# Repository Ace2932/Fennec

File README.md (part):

# Fennec — Autonomous Quadruped

> **Fennec** is an autonomous quadruped I'm building on the [NovaSM3](https://github.com/cguweb-com/Arduino-Projects/tree/main/Nova-SM3) platform (by Chris Locke / [novaspotmicro.com](https://novaspotmicro.com/)) — rebuilt around a unified Feetech STS3215 TTL servo bus, NVIDIA Jetson Orin Nano Super compute, and ROS 2 Humble, as a platform for Vision-Language-Action (VLA) model deployment, 3D SLAM, and autonomous mobile manipulation.

**Status:** 🔧 Phase 1 — hardware bring-up + sim training. **Both PCBs ordered 2026-07-01 (JLCPCB)** — power board v2 (Pattern B bus master, INA226 rail telemetry, Phase-4 arm rail provisioned) + logic board. Firmware critical-path green (safety FSM, watchdogs, servo limits, joint-map loader; rostest suites in CI). Legs (**leg_v6**) printing; chassis-integration + CAD fit-gate audits closed; measured leg geometry → URDF + IK green. **🎉 RL locomotion walks in sim** (MuJoCo MJX + Brax PPO, 2026-07-16) — stair-climb curriculum in progress. **See [`STATUS.md`](./STATUS.md) for the live blockers / next-actions board.**
**Platform:** Quadruped (12 DOF) — arm (6-DOF, Phase 4 future) on shelf
**Compute:** NVIDIA Jetson Orin Nano Super 8GB
**Middleware:** ROS 2 Humble
**Last updated:** July 22, 2026

---

> **Design outline:** [`docs/design-outline.md`](./docs/design-outline.md) — the canonical top-level design document (architecture, doctrines, lane status). Start there.

## Table of Contents

1. [Project Overview](#project-overview)
2. [Differences from Stock NovaSM3](#differences-from-stock-novasm3)
3. [Hardware Architecture](#hardware-architecture)
4. [Software Architecture](#software-architecture)
5. [Power System](#power-system)
6. [Network Topology](#network-topology)
7. [Bill of Materials](#bill-of-materials)
8. [Build Roadmap](#build-roadmap)
9. [Pre-Assembly Test Sequence](#pre-assembly-test-sequence)
10. [Setup Guide](#setup-guide)
11. [Open Decisions](#open-decisions)
12. [References & Credits](#references--credits)

---

## Project Overview

This project is a heavily modified fork of the open-source NovaSM3 quadruped, redesigned to serve as a research platform for embodied AI. Stock Nova uses PWM hobby servos and a Raspberry Pi running custom locomotion code. This build replaces:

- **12 servos** with Feetech STS3215 TTL bus servos for unified protocol, real-time joint feedback (position, load, temperature, voltage), and elimination of PWM wiring complexity. Six additional STS3215 (arm) remain on shelf for Phase 4.
- **The Pi** with an NVIDIA Jetson Orin Nano Super (67 TOPS sparse INT8 / ~33 TOPS dense; 8GB RAM tight but workable for VLA inference + ROS 2 + SLAM — see Phase 4 notes). Real-time servo bus is offloaded to a Teensy 4.1 (Pattern B); Jetson runs ROS 2 + perception only.
- **The stock perception** with Intel RealSense D456 (depth + RGB + IMU) and Unitree L2 4D LiDAR (360° × 96° FOV, 30m range)
- **The stock locomotion stack** with ROS 2 Humble (Jetson) + Teensy bus master (Pattern B) + Nav2 + RTAB-Map / POINT-LIO

The arm is carried over from a prior SO-ARM101 build, also Feetech-based. **v1 build scope: quadruped only (12 servos active).** Arm install + integration is Phase 4 future work — bus IDs 13-18 and the 7.5V arm-rail buck footprint (D42V55F7) are reserved on the PCB v6 redesign so the future install is a populate-and-go.

### Goals

- ✅ Unified TTL servo bus across locomotion (12 servos v1; future-ready for 18 with arm)
- 🔧 ROS 2 locomotion via micro-ROS bridge to Teensy 4.1 (Teensy owns the Feetech bus in Pattern B; FE-URT-1 retained as bench fallback)
- 🔧 RL locomotion policy trained in simulation (`sim/nova_mjx`, MuJoCo MJX + Brax PPO) — ✅ walks in sim (2026-07-16); terrain curriculum + stair climbing + sim2real transfer in progress
- 📋 3D SLAM using LiDAR + visual-inertial fusion (POINT-LIO baseline, RTAB-Map comparison)
- 📋 Autonomous navigation (Nav2) on legged platform with stair climbing
- 📋 VLA fine-tuning and deployment for mobile manipulation tasks
- 📋 Open-source documentation of every design decision for community reuse

---

## Differences from Stock NovaSM3

| Subsystem | Stock NovaSM3 | This Build |
|-----------|---------------|------------|
| Compute (main) | Raspberry Pi 4 | NVIDIA Jetson Orin Nano Super 8GB |
| Compute (MCU) | Teensy 4.0 | Teensy 4.1 (more RAM + SD slot) |
| Aux MCU | Arduino Nano | Arduino Nano (kept, peripherals only) |
| Locomotion servos | 12× PWM hobby servos | 12× Feetech STS3215 (4× 12V/30kg hip, 8× 7.4V/19kg femur/tibia) |
| Arm | None (stock) | 6× Feetech STS3215 from SO-ARM101 — **on shelf, Phase 4** |
| Servo protocol | PWM (one signal per servo) | TTL half-duplex serial bus (daisy-chained) |
| Perception | None / optional | RealSense D456 + Unitree L2 LiDAR |
| Middleware | Custom Arduino loops | ROS 2 Humble + micro-ROS |
| Power | 3S 11.1V LiPo | 4S 14.8V LiPo + Pololu buck rails (7.5V leg / 12V hip / 12V L2 dedicated / 12V Jetson / 5V aux). XL4016 dropped after capacity audit. |
| Print materials | PLA / PETG | PA6-CF (structural) / PETG-CF (secondary) / TPU 95A (foot pads + strain relief) |
| Print feed | Direct from spool | **Creality SpacePi X4 dryer → 4 mm PTFE Bowden → P1S** (AMS HF bypassed for PA6-CF — re-absorbs moisture in AMS chamber, defeats pre-drying) |

### Why redesign the PCB (v5.2b → v6)

After the v3.2 architecture audit, the stock Nova PCB v5.2b can't host the upgraded power tree (Pololu modules, INA226 telemetry, hard-cutoff MOSFET, E-stop chain) or the Pattern A/B bus master selector. The redesign retains the spirit of the stock board (Arduino Nano aux slot, battery input geometry) and adds the new safety + power architecture. Full feature set in [`hardware/pcb-mods/README.md`](./hardware/pcb-mods/README.md).

### What carries over from Nova v5.2b

- Arduino Nano slot for aux peripherals — **v3.5 cut**: OLED + WS2812B only (PIR / ultrasonic / MP3 / MPU-6050 removed; D456 + L2 perception stack covers their roles)
- Battery input + reverse polarity protection geometry (replicated with MOSFET-based reverse protection instead of diode)
- Power switch, voltmeter, fuse (MRBF-30 in Blue Sea 5191 block, OFF-board at pack — ~9 kA AIC @ 16.8 V clears this pack's ~1.5–3 kA dead-short with 3–4× margin; ANL's 6 kA rejected, Class T superseded 2026-06-12)

### What changes

- All 12 PWM servo output headers removed (Feetech bus is daisy-chain TTL, doesn't use PWM)
- XL4016 buck footprints → Pololu D42V110-class module footprints
- Add: SN74LVC125A half-duplex driver (Pattern B prep), INA226 ×3, E-stop chain, hard-cutoff MOSFET, **MRBF-30 fuse OFF-board** (Blue Sea 5191 at pack — F1 not on PCB), bulk caps at injection points, bus-integrity footprints (series R + ferrite beads), reserved arm-rail buck footprint

---

## Hardware Architecture

### Block diagram

```
┌────────────────────────────────────────────────────────────────────┐
│                  NVIDIA Jetson Orin Nano Super 8GB                 │
│                          (ROS 2 Humble)                            │
│   • Nav2, SLAM, VLA inference, sensor fusion                       │
│   • Sends /joint_commands to Teensy via micro-ROS over USB         │
│   • Built-in WiFi 5 (802.11ac/ab/gn) per NVIDIA P3766 spec sheet   │
└──┬──────────┬─────────────┬─────────────┬───────────────────────────┘
   │ USB-C    │ USB 3.1     │ Ethernet    │ USB (micro-ROS transport)
   │          │             │             │
┌──▼───────┐ ┌▼───────────┐ ┌▼───────────┐ ┌▼─────────────────────────┐
│ Realsense│ │ FE-URT-1   │ │ Gig switch │ │ Teensy 4.1 (BUS MASTER v1)│
│ D456     │ │ (debug/    │ │            │ │  • Real-time gait loop    │
│ (depth + │ │  bench     │ │ ◄─ L2 ─►   │ │  • UART → SN74LVC125A → bus   │
│  RGB +   │ │  fallback) │ │            │ │  • INA226 I²C reader      │
│  IMU)    │ │            │ └────────────┘ │  • E-stop GPIO sense      │
└──────────┘ └────┬───────┘                │  • micro-ROS over USB     │
                  ↓                        └──┬────────────────────────┘
              (JP_BUS_MASTER                  │ UART → SN74LVC125A half-duplex
               solder bridge:                 │ (active v1 path)
               default = B,                   │
               flip to A for ID setup)        ▼
                                  ┌───────────────────────┐
                                  │ 12× STS3215 (TTL bus) │
                                  │ per-leg: FL1-3 FR4-6  │
                                  │ RL7-9 RR10-12 (h/f/t) │
                                  │  IDs 13-18: ⏸ arm    │
                                  │  (Phase 4 reserved)   │
                                  └───────────────────────┘

       ┌──── Arduino Nano (USB-serial bridge from Jetson:
       │                   OLED + WS2812B status LEDs) ────┐
       │                                                                  │
       └──────────────────────────────────────────────────────────────────┘
```

### Servo configuration

| Joint group | Count | Servo | Voltage | Bus IDs | Status |
|-------------|-------|-------|---------|---------|--------|
| Hips | 4 | STS3215 30kg | 12V | 1-4 | v1 active |
| Femur + tibia | 8 | STS3215 19kg | 7.4V | 5-12 | v1 active |
| Arm (shoulder + elbow) | 3 | STS3215 19kg | 7.4V | 13-15 | ⏸ Phase 4 — reserved |
| Arm (wrist + gripper) | 3 | STS3215 19kg | 7.4V | 16-18 | ⏸ Phase 4 — reserved |

**v1 build = 12 active servos** on a single daisy-chained TTL bus, 2 active servo-power voltage levels (7.5V leg, 12V hip) plus dedicated 12V/2.6A L2 LiDAR buck and 12V/3A Jetson buck. Bus master is the **Teensy 4.1 (Pattern B)** via a SN74LVC125A half-duplex driver. Bus IDs 13-18 and the 7.4V arm rail (D42V55F7 footprint) reserved on PCB v6 for Phase 4 arm install — populate-and-go.

### Bus master pattern

**Pattern B is v1 default.** Both paths live on PCB v6 via solder bridge `JP_BUS_MASTER`.

- **Pattern B (v1 active):** Teensy 4.1 hardware UART → SN74LVC125A quad tri-state buffer (half-duplex driver) → TTL bus pads. Bare-metal real-time loop at 200-500 Hz. Jetson sends joint targets via micro-ROS over USB; Teensy translates to bus reads/writes. Survives Jetson restarts, kernel preemption, CUDA stalls, journald flushes — none of which affect bus servicing. Solder bridge defaults to B.
- **Pattern A (bench / debug fallback):** Jetson → USB → FE-URT-1 → TTL bus. Use for: initial servo ID assignment with the Feetech FD / SCServo SDK Python tools from a workstation (simpler than booting micro-ROS for ID setup), debug if Teensy firmware misbehaves, post-mortem inspection of bus traffic. Flip `JP_BUS_MASTER` to A.

**Why B as default (decision history):** Linux is not a real-time OS. USB-CDC latency on Jetson runs 1-10 ms typical, 50 ms+ under load. **What Pattern B actually buys:** bus-servicing isolation on the Teensy side — UART transactions to all 12 servos complete on time even when Jetson is jittery, so the bus doesn't time out and servos don't fault. The gait controller still runs on Jetson and publishes targets at 100 Hz, so Jetson's command rate is still Linux-bounded; the Teensy oversamples at 200-500 Hz against the last received target, holding it through Jetson stalls. A 100 ms Linux freeze becomes "robot pauses mid-step," not "bus dies and robot falls." v3.2 originally defaulted to A with "migrate if measurement forces it" — v3.3 flips to B-default because the migration cost is just populating one $1 IC + Phase 1 firmware work, and skipping the measure-then-migrate path eliminates a Phase 2 surprise. See Open Decisions row 5.

**Phase 1 acceptance gate (revised):** Pattern B's real guarantee is bus-servicing isolation on the Teensy side, not full RTT through Linux. Two mandatory criteria + one sanity check:
1. **Teensy local loop tick jitter p99 <100 µs** over 60 seconds (bare-metal — easy if firmware is right)
2. **`/joint_commands` arrival rate ≥99% of 100 Hz target** over 60 seconds (Jetson + uROS healthy)
3. *(Sanity)* End-to-end RTT median <5 ms, p99 <20 ms — Linux-bounded, not a hard pass/fail

If (1) misses → debug Teensy firmware (DMA vs ISR, UART config). If (2) misses → debug Jetson uROS / USB cable / CPU contention. If only (3) is high → accept: Teensy holds last command under Jetson jitter, robot stays stable.

---

## Software Architecture

### ROS 2 stack (target)

```
┌──────────────────────────────────────────────┐
│             Application Layer                │
│  • Behavior tree / mission FSM               │
│  • VLA policy node                           │
│  • Teleop bridge                             │
└──────────────────────────────────────────────┘
┌──────────────────────────────────────────────┐
│            Navigation Layer                  │
│  • Nav2 (planning + control)                 │
│  • robot_localization (EKF)                  │
└──────────────────────────────────────────────┘
┌──────────────────────────────────────────────┐
│              Perception Layer                │
│  • RTAB-Map / POINT-LIO (3D SLAM)            │
│  • realsense2_camera                         │
│  • unitree_lidar_ros2                        │
└──────────────────────────────────────────────┘
┌──────────────────────────────────────────────┐
│            Locomotion Layer (Jetson)         │
│  • Gait controller (8-phase walk)            │
│  • 3-DOF-per-leg IK solver                   │
│  • Publishes /joint_commands                 │
│  • Subscribes /joint_states                  │
└──────────────────────────────────────────────┘
┌──────────────────────────────────────────────┐
│        Bus Master Layer (Teensy 4.1)         │
│  • micro-ROS client (USB transport)          │
│  • SCServo SDK port — Feetech bus driver     │
│  • SN74LVC125A half-duplex TX/RX gating          │
│  • Real-time loop @ 200-500 Hz               │
│  • INA226 I²C reader → /diagnostics          │
└──────────────────────────────────────────────┘
┌──────────────────────────────────────────────┐
│              Hardware Layer                  │
│  • Feetech STS3215 bus (12 servos v1)        │
│  • IMU driver, aux peripheral I/O            │
└──────────────────────────────────────────────┘
```

### Key software components

| Component | Purpose | Status |
|-----------|---------|--------|
| ROS 2 Humble | Middleware | 📋 Install on Jetson |
| `librealsense2` | RealSense SDK | 📋 ARM64 build |
| `realsense2_camera` | ROS 2 wrapper for D456 | 📋 apt install |
| `unilidar_sdk2` | Unitree L2 SDK | ✅ Built green on Jetson (official `unitreerobotics/unilidar_sdk2`, **not discodyer fork** — official now bundles ROS 2 wrapper) |
| `unitree_lidar_ros2` | ROS 2 wrapper for L2 | ✅ Built + streaming. Use **Ace2932/unilidar_sdk2 `fix/imu-bridge-double-call` branch** — fixes upstream IMU bridge bug where `getImuData()` is called twice in `timer_callback()`, draining the SDK queue before publish. |
| POINT-LIO | LiDAR-inertial SLAM | 📋 Eval first |
| RTAB-Map | Visual-LiDAR SLAM | 📋 Compare with POINT-LIO |
| Nav2 | Autonomous navigation | 📋 Phase 3 |
| robot_localization | EKF sensor fusion | 📋 Phase 2 |
| micro-ROS (Teensy) | Embedded ROS 2 | 📋 Phase 2 |
| SCServo SDK (Teensy port) | Feetech bus driver running on Teensy in Pattern B | ⚠️ Already familiar from SO-ARM101 — port to TeensyDuino in Phase 1 |
| MJX/Brax sim (`sim/nova_mjx`) | RL locomotion training — MuJoCo MJX physics, Brax PPO, procedural terrain curriculum (rough / steps / stairs), domain randomization | 🔧 Walks in sim (flat trot, 2026-07-16); stair-climb curriculum active |

---

## Power System

### Voltage rails

```
4S LiPo 14.8V nominal (12.8-16.8V)
   │  MRBF-30 fuse (off-board) · MOSFET reverse-protection · MOSFET hard-cutoff @12.4V · E-stop NC (servo rails only)
   │
   ├── Pololu D42V110F7  ──► 7.5V/10A ──► 8× STS3215 19kg femur/tibia
   │       (star injection at 4 points along chain, bulk caps near point of load)
   │
   ├── Pololu D42V110F12 ──► 12V/9A   ──► 4× STS3215 30kg hips ONLY
   │
   ├── Pololu D24V22F12  ──► 12V/2.6A ──► Unitree L2 LiDAR (1A, LC filter on output)
   │
   ├── Pololu D42V55F12  ──► 12V/~3A  ──► Jetson Orin Nano (barrel jack)
   │
   ├── [reserved D42V55F7] ► 7.5V/3-8A ──► 6× STS3215 arm (Phase 4 — footprint unstuffed)
   │
   └── UBEC 5V/5A ──► 5V rail ──► fans, aux 5V peripherals

   INA226 ×3 (leg 7.5V, hip 12V, Jetson 12V) ──► I²C ──► Teensy 4.1 ──► ROS 2 diagnostics
   13.0V comparator ──► Teensy GPIO ──► /battery_low ──► Jetson clean shutdown
   12.4V comparator ──► MOSFET ──► breaks battery feed (autonomous backstop)
```

### Notes

- All rails share a common ground
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
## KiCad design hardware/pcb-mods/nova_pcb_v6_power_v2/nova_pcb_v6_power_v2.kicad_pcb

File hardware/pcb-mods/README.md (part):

# NovaSM3 PCB v6 — Design Spec

Custom PCB replacing the upstream NovaSM3 v5.2b. Driven by the v3.2 architecture audit:
- XL4016 buck rails undersized for walking-gait current (8A cont. vs measured 8-12A avg + 25-40A impact transients)
- No safety chain (no LVC, no E-stop, no per-rail telemetry, no fuse spec)
- No Pattern B prep (any future Teensy-owns-bus migration requires chassis teardown)
- Stock PWM servo headers unused (Feetech bus is daisy-chain TTL)

Reference: BOM v3.2 §2, §3 · [`docs/power-budget.md`](../../docs/power-budget.md) · README "Power System" section.

---

## Feature set (v6 must-have)

### 1. Battery input + reverse protection

- XT60 panel-mount input (matches Ovonic packs)
- **MOSFET-based reverse-polarity protection** (not a diode — too much Vdrop at 10-15A continuous)
- **MRBF-30 terminal fuse — OFF-BOARD**, Blue Sea 5191 block at the pack in the battery→PCB lead (not a PCB footprint; F1 removed from `nova_pcb_v6` 2026-06-04). 30A time-delay, sized for hip-rail worst case ~20A + headroom. ANL/MIDI's ~6 kA interrupt rating can "fail to interrupt" a LiPo dead-short (vapor reconducts) → rejected. Class T (20 kA) was the interim spec, but this single 4S pack's real Isc ≈ 16.8 V ÷ 6–12 mΩ ≈ **1.5–3 kA**, vs MRBF's **~9 kA AIC @ 16.8 V = 3–4× margin** at ⅓ the size/weight → **MRBF chosen 2026-06-12**. At-source placement also protects the battery→PCB cable. See [`docs/research/2026-05-17-notes.md`](../../docs/research/2026-05-17-notes.md) §9 + [`docs/order-list.md`](../../docs/order-list.md) MRBF section.
- Power switch (off-board Blue Sea Contura SPST, **~18A @ 16.8 V DC**; 20A@12V / 15A@24V) wiring to on-board SW1 block. Sized for ~14A sustained; the SW1 terminal block matches it (15–20A class). The 30A MRBF is catastrophic-short (kA) protection, **not** the switch-path thermal limit — so SW1 block + switch are intentionally rated below the fuse.
- Mini digital voltmeter retained for at-a-glance pack state

### 2. Four active power rails + one reserved (v3.4 split)

| Rail | Module | Output | Sized for | Status |
|------|--------|--------|-----------|--------|
| Leg | Pololu D42V110F7 | 7.5V / 10A typ @ 42V Vin | 8× STS3215 19kg | Active v1 |
| Hip | Pololu D42V110F12 | 12V / 9A typ @ 42V Vin | 4× STS3215 30kg ONLY | Active v1 |
| L2 LiDAR | Pololu D24V22F12 | 12V / 2.6A | Unitree L2 (1A, dedicated buck for clean power) | Active v1 (added v3.4) |
| Jetson | Pololu D42V55F12 | 12V / ~3A cont. | Jetson Orin Nano Super MAXN | Active v1 |
| Arm | Pololu D42V55F7 | 7.5V / 3-8A | 6× STS3215 arm (Phase 4) | **Footprint reserved — DO NOT populate v1** |
| Aux 5V | UBEC 5V/5A (off-board) | 5V / 5A | Fans, aux peripherals | Header on board |

Module footprints use Pololu's standard header pitch so cards can be swapped without PCB respin. L2 split from hip rail (v3.4) because D42V110F12's 9A typ @ 42V Vin derates to ~7-8A at our 14.8V Vin, and combined hip+L2 sustained ~9A was over budget.

**Buck modules are OFF-BOARD (2026-06-05).** All five Pololu cards mount in a 3D-printed finned holder (open-air cooling), NOT soldered to the PCB. Forcing reason: every Pololu module is 100 % THT, so on-board the two PCB faces are **not independent placement planes** — pins pierce both. The 5 bucks alone are 47 % of the 112×90 board on a single plane, which pushes the all-THT board to ~74-84 % packing (hand-solder ceiling ≈55 %): it does not fit and is not hand-solderable. Off-board frees ~half the board and cools the bucks better than sandwiching them in the 20 mm mezzanine gap. The PCB keeps the buck **wire-terminal landings** at U1-U5 (footprint swap module → terminal, **netlist untouched** — same move as the INA226 swap). The finned holder is a CAD task tracked separately.

### 3. Servo bus distribution (star injection)

- Single signal bus (daisy-chained TTL) — no break
- **4 power injection points** along the leg 7.5V trunk (one per leg pair)
- **Bulk caps (1000 µF / 25V) at each injection point** — soaks impact transients near point of load
- GND-plane reference (FE-URT-1; solid GND plane = single low-Z return)
- Hip rail injects at chassis floor (4 hips clustered there)

### 4. Bus master — Pattern B default, Pattern A fallback

**Pattern B is the v1 active path.** Teensy 4.1 hardware UART routed through **SN74LVC125A quad tri-state buffer** as a half-duplex driver to the Feetech TTL bus pads. The SN74LVC125A must be populated on first build.

- Teensy UART TX → SN74LVC125A input gate
- Teensy GPIO → SN74LVC125A OE pins (TX-enable for write, RX-enable for read; half-duplex direction control)
- SN74LVC125A output → bus signal pad
- FE-URT-1 USB→TTL input header retained for fallback

Solder bridge `JP_BUS_MASTER` selects which path drives the bus pads:

- **B (default — board ships configured this way):** Teensy UART → SN74LVC125A → bus
- **A (fallback):** FE-URT-1 → bus directly (used for ID setup, debug, post-mortem)

Both paths terminate on the same bus pads; the bridge is the only state change. No chassis teardown to swap.

Linux jitter rationale: USB-CDC latency on Jetson is 1-10 ms typical, 50 ms+ under CUDA / kworker / journald load. Pattern B isolates the bus-servicing side (Teensy completes UART transactions to all 12 servos on time even when Jetson stalls); the gait command rate from Jetson is still Linux-bounded but the Teensy holds-last-command at 200-500 Hz, so a 100 ms Jetson freeze becomes a mid-step pause instead of a bus timeout.

### 5. Bus integrity footprints (populate per measured error rate)

Feetech bus is **single-ended half-duplex TTL UART**, not RS-485. 120 Ω differential termination is the wrong tool here.

- Series R footprints (22-100 Ω, 0603) at FE-URT-1 / SN74LVC125A output — slope rate-limiting
- Ferrite bead footprints at each servo entry — common-mode noise rejection
- GND-plane reference (FE-URT-1; solid GND plane = single low-Z return)

Default v1 build: leave footprints unpopulated. Populate iteratively if bus error rate exceeds threshold during bring-up. If still poor, drop baud 1M → 500k → 250k.

### 6. Safety chain

Three-stage battery low-voltage chain (highest trip first):
- **Charger LVC alarm:** ISDT 608AC set to **3.3V/cell = 13.2V** (warning beep, user-facing)
- **Graceful-shutdown comparator:** **3.25V/cell = 13.0V** pack. Comparator (LM393) + resistor divider → Teensy GPIO input. Teensy debounces + publishes `/battery_low`. Jetson subscribes + runs `systemctl poweroff` to unmount SD cleanly. ~30-60 s window before the hard cutoff trip at typical discharge rates — enough for Jetson to halt.
- **MOSFET hard-cutoff:** **3.1V/cell = 12.4V** pack. Second comparator stage drives a logic-level MOSFET on the battery feed. Autonomous backstop — fires whether or not Jetson shut down per the 13.0V trigger.

Other safety:
- **E-stop:** panel-mount latching button, NC contact. Wired in series with the **leg + hip + L2 rail enable lines** (D42V110F7 + D42V110F12 + D24V22F12 EN pins). Killing L2 stops the LiDAR spinning under emergency. Jetson rail stays alive for post-mortem debug + telemetry capture. Twist-to-release.
- **INA226 ×4:** one per active rail (leg 7.5V @0x40, hip 12V @0x41, Jetson 12V @0x44, L2 12V @0x45 — the L2 monitor is U12, populated, not optional since 2026-06-30). I²C bus to Teensy 4.1 → ROS 2 diagnostics topic. Per-rail current/voltage telemetry. **All four are identical 2 mΩ-shunt breakout modules** (Adafruit INA226 / "20A" generic) on 2.54 mm THT headers — the module's onboard shunt closes the high-side sense loop, so there is **no bare VSSOP-10 chip and no external 2512 shunt** (was the v1 plan for leg/hip; standardized to modules 2026-06-04). Must be a **2 mΩ** board: cheap 0.1 Ω "meter" modules saturate above ~0.8 A (useless on 8-12 A rails). Net effect: the board now has **zero fine-pitch parts** — everything is THT or 1.27 mm SOIC / SOT-23.

### 7. Aux MCU + peripherals (carryover from Nova v5.2b)

- Arduino Nano slot (3-pack already owned). **BOM v3.5 cut: only SSD1331 OLED + WS2812B LEDs remain active.** PIR / ultrasonic / DFPlayer / MPU-6050 dropped (redundant with D456 + L2 perception stack). Nano now acts as USB-serial bridge from Jetson driving the OLED (SPI) + LED strip (1 GPIO).
- Teensy 4.1 footprint (already owned) for INA226 I²C reader, E-stop GPIO, Pattern B half-duplex driver

### 8. Mechanical / connector convention

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
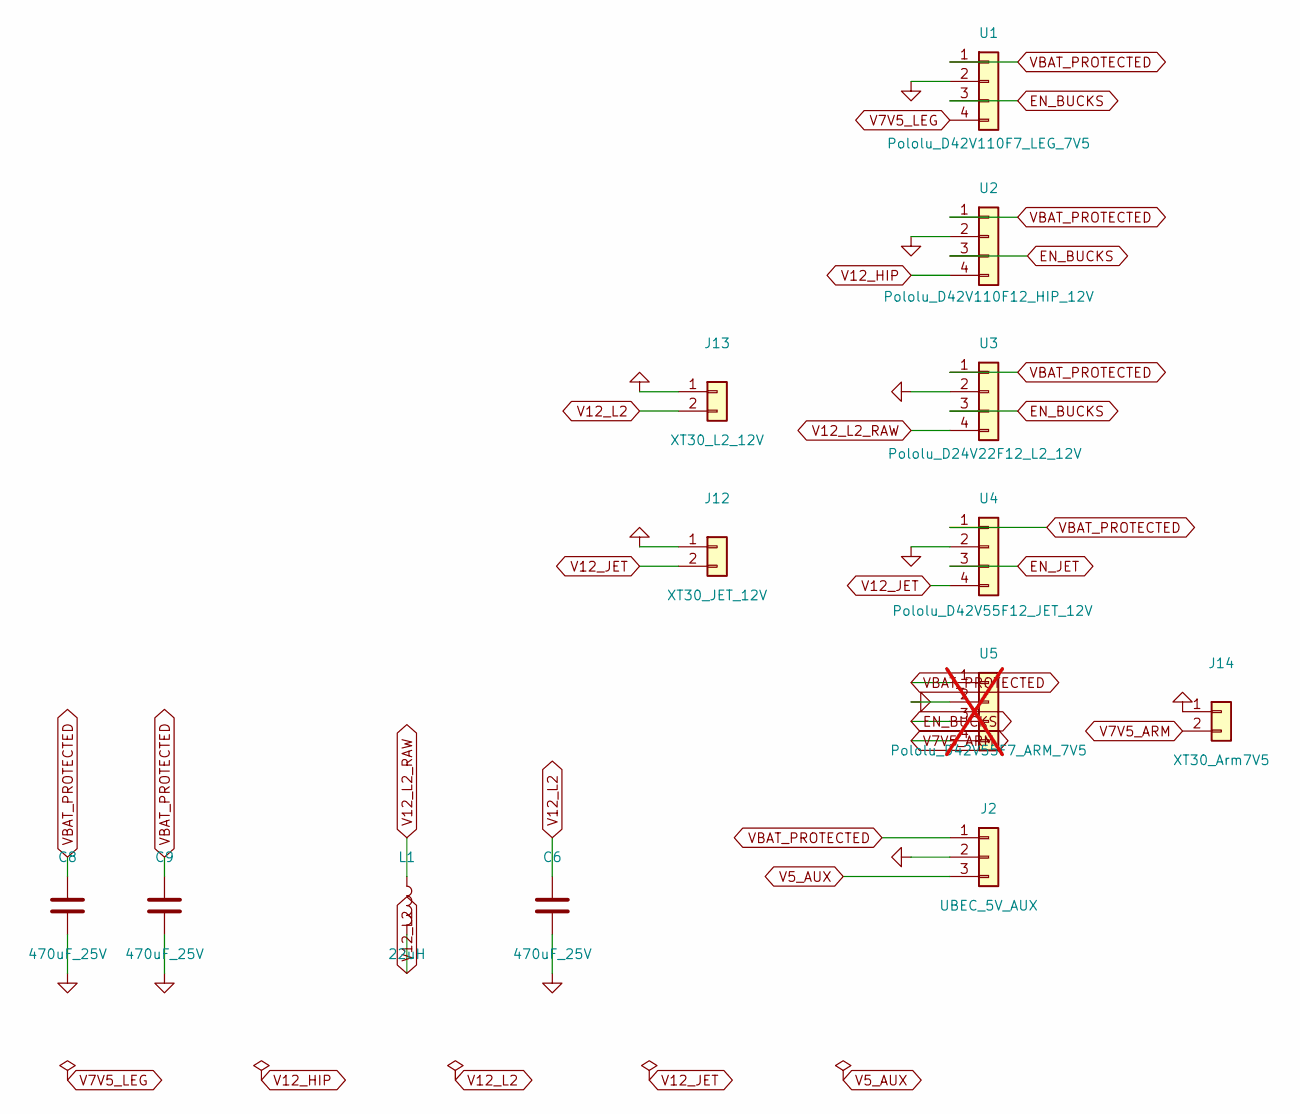
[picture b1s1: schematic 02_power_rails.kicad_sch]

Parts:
C6, C8, C9: 470uF_25V; CP_Radial_D10.0mm_P5.00mm; MPN UPW1E471MPD; DigiKey 493-1826-ND
J2: UBEC_5V_AUX; PinHeader_1x03_P2.54mm_Vertical; MPN PRPC040SAAN-RC; DigiKey S1011EC-40-ND
J12: XT30_JET_12V; AMASS_XT30U-M_1x02_P5.0mm_Vertical; MPN XT30U-M
J13: XT30_L2_12V; AMASS_XT30U-M_1x02_P5.0mm_Vertical; MPN XT30U-M
J14: XT30_Arm7V5; AMASS_XT30U-M_1x02_P5.0mm_Vertical; MPN XT30U-M
L1: 22uH; L_12x12mm_H8mm; MPN SRR1260-220M; DigiKey SRR1260-220MCT-ND
U1: Pololu_D42V110F7_LEG_7V5; Buck_Offboard_Terminal_2xXT30; MPN D42V110F7
U2: Pololu_D42V110F12_HIP_12V; Buck_Offboard_Terminal_2xXT30; MPN D42V110F12
U3: Pololu_D24V22F12_L2_12V; Buck_Offboard_Terminal_2xXT30; MPN D24V22F12
U4: Pololu_D42V55F12_JET_12V; Buck_Offboard_Terminal_2xXT30; MPN D42V55F12
U5: Pololu_D42V55F7_ARM_7V5; Buck_Offboard_Terminal_2xXT30; MPN D42V55F7; not fitted

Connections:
EN_BUCKS: U1.3, U2.3, U3.3, U5.3; also elsewhere on the board
EN_JET: U4.3; also elsewhere on the board
GND: C6.2, C8.2, C9.2, J2.2, J12.1, J13.1, J14.1, U1.2, U2.2, U3.2, U4.2, U5.2; also elsewhere on the board
V5_AUX: J2.3; also elsewhere on the board
V7V5_ARM: J14.2, U5.4
V7V5_LEG: U1.4; also elsewhere on the board
V12_HIP: U2.4; also elsewhere on the board
V12_JET: J12.2, U4.4
V12_L2: C6.1, J13.2, L1.2
V12_L2_RAW: L1.1, U3.4
VBAT_PROTECTED: C8.1, C9.1, J2.1, U1.1, U2.1, U3.1, U4.1, U5.1; also elsewhere on the board

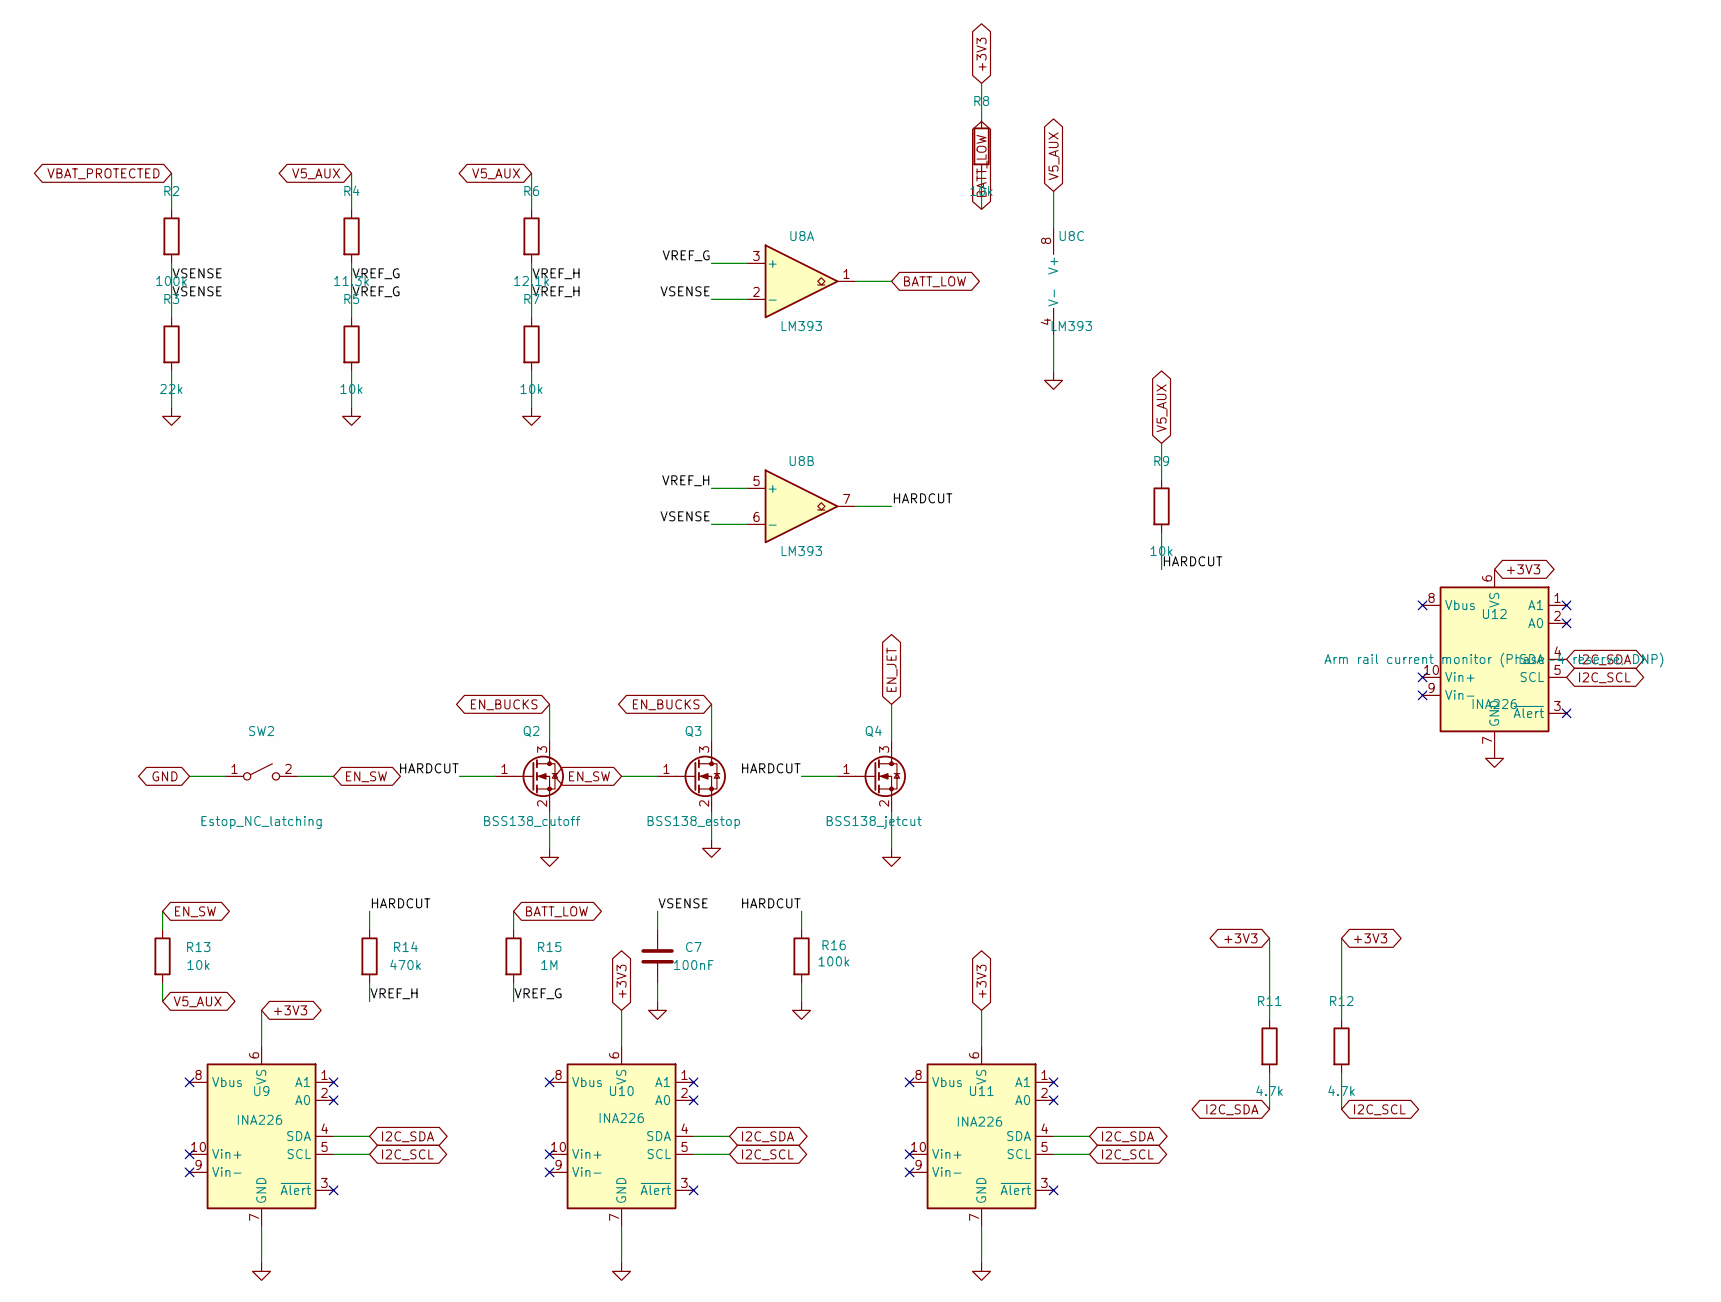
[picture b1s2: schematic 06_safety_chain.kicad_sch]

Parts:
C7: 100nF; C_0603_1608Metric; MPN CC0603KRX7R9BB104; DigiKey 311-1344-1-ND
Q2: BSS138_cutoff; SOT-23; MPN BSS138; DigiKey BSS138CT-ND
Q3: BSS138_estop; SOT-23; MPN BSS138; DigiKey BSS138CT-ND
Q4: BSS138_jetcut; SOT-23; MPN BSS138; DigiKey BSS138CT-ND
R2, R16: 100k; R_0603_1608Metric; MPN RC0603FR-07100KL; DigiKey 311-100KHRCT-ND
R3: 22k; R_0603_1608Metric; MPN RC0603FR-0722KL; DigiKey 311-22.0KHRCT-ND
R4: 11.3k; R_0603_1608Metric; MPN RC0603FR-0711K3L; DigiKey 311-11.3KHRCT-ND
R5, R7, R8, R9, R13: 10k; R_0603_1608Metric; MPN RC0603FR-0710KL; DigiKey 311-10.0KHRCT-ND
R6: 12.1k; R_0603_1608Metric; MPN RC0603FR-0712K1L; DigiKey 311-12.1KHRCT-ND
R11, R12: 4.7k; R_0603_1608Metric; MPN RC0603FR-074K7L; DigiKey 311-4.70KHRCT-ND
R14: 470k; R_0603_1608Metric; MPN CRCW0603470KFKEA; DigiKey 541-470KHCT-ND
R15: 1M; R_0603_1608Metric; MPN RC0603FR-071ML; DigiKey 311-1.00MHRCT-ND
SW2: Estop_NC_latching; TerminalBlock_Philmore_TB132_1x02_P5.00mm_Horizontal; MPN KF301-5.0-2P
U8: LM393; SOIC-8_3.9x4.9mm_P1.27mm; MPN LM393DR; DigiKey 296-1015-1-ND
U9, U10, U11, U12: INA226; INA226_Module_Breakout; MPN INA226-20A-R002-MODULE

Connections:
+3V3: R8.1, R11.1, R12.1, U9.6 (VS), U10.6 (VS), U11.6 (VS), U12.6 (VS); also elsewhere on the board
/06 Safety Chain/HARDCUT: Q2.1 (G), Q4.1 (G), R9.2, R14.1, R16.1, U8.7
/06 Safety Chain/VREF_G: R4.2, R5.1, R15.2, U8.3 (+)
/06 Safety Chain/VREF_H: R6.2, R7.1, R14.2, U8.5 (+)
/06 Safety Chain/VSENSE: C7.1, R2.2, R3.1, U8.2 (-), U8.6 (-)
BATT_LOW: R8.2, R15.1, U8.1; also elsewhere on the board
EN_BUCKS: Q2.3 (D), Q3.3 (D); also elsewhere on the board
EN_JET: Q4.3 (D); also elsewhere on the board
EN_SW: Q3.1 (G), R13.1, SW2.2 (B)
GND: C7.2, Q2.2 (S), Q3.2 (S), Q4.2 (S), R3.2, R5.2, R7.2, R16.2, SW2.1 (A), U8.4 (V-), U9.7 (GND), U10.7 (GND), U11.7 (GND), U12.7 (GND); also elsewhere on the board
I2C_SCL: R12.2, U9.5 (SCL), U10.5 (SCL), U11.5 (SCL), U12.5 (SCL); also elsewhere on the board
I2C_SDA: R11.2, U9.4 (SDA), U10.4 (SDA), U11.4 (SDA), U12.4 (SDA); also elsewhere on the board
V5_AUX: R4.1, R6.1, R9.1, R13.2, U8.8 (V+); also elsewhere on the board
VBAT_PROTECTED: R2.1; also elsewhere on the board

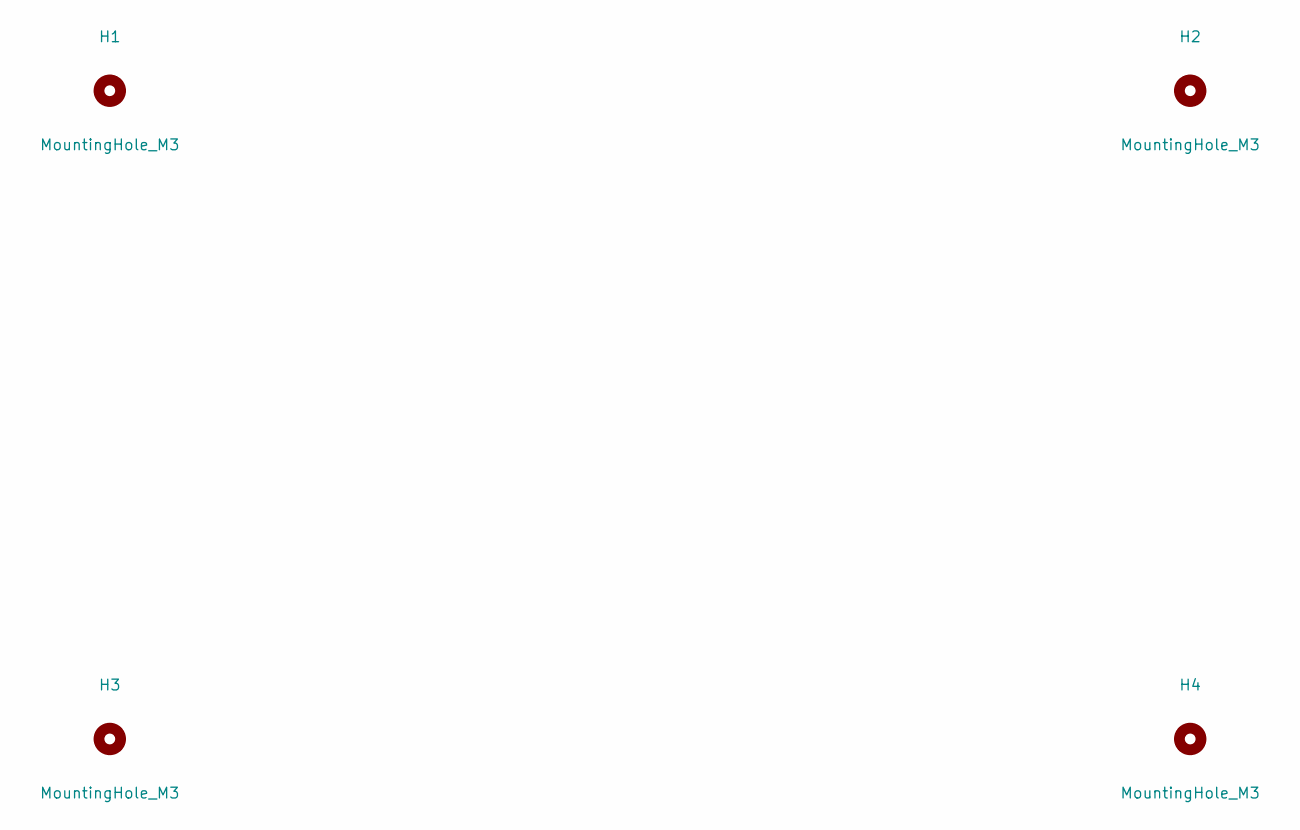
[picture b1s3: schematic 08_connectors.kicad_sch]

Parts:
H1, H2, H3, H4: MountingHole_M3; MountingHole_3.2mm_M3

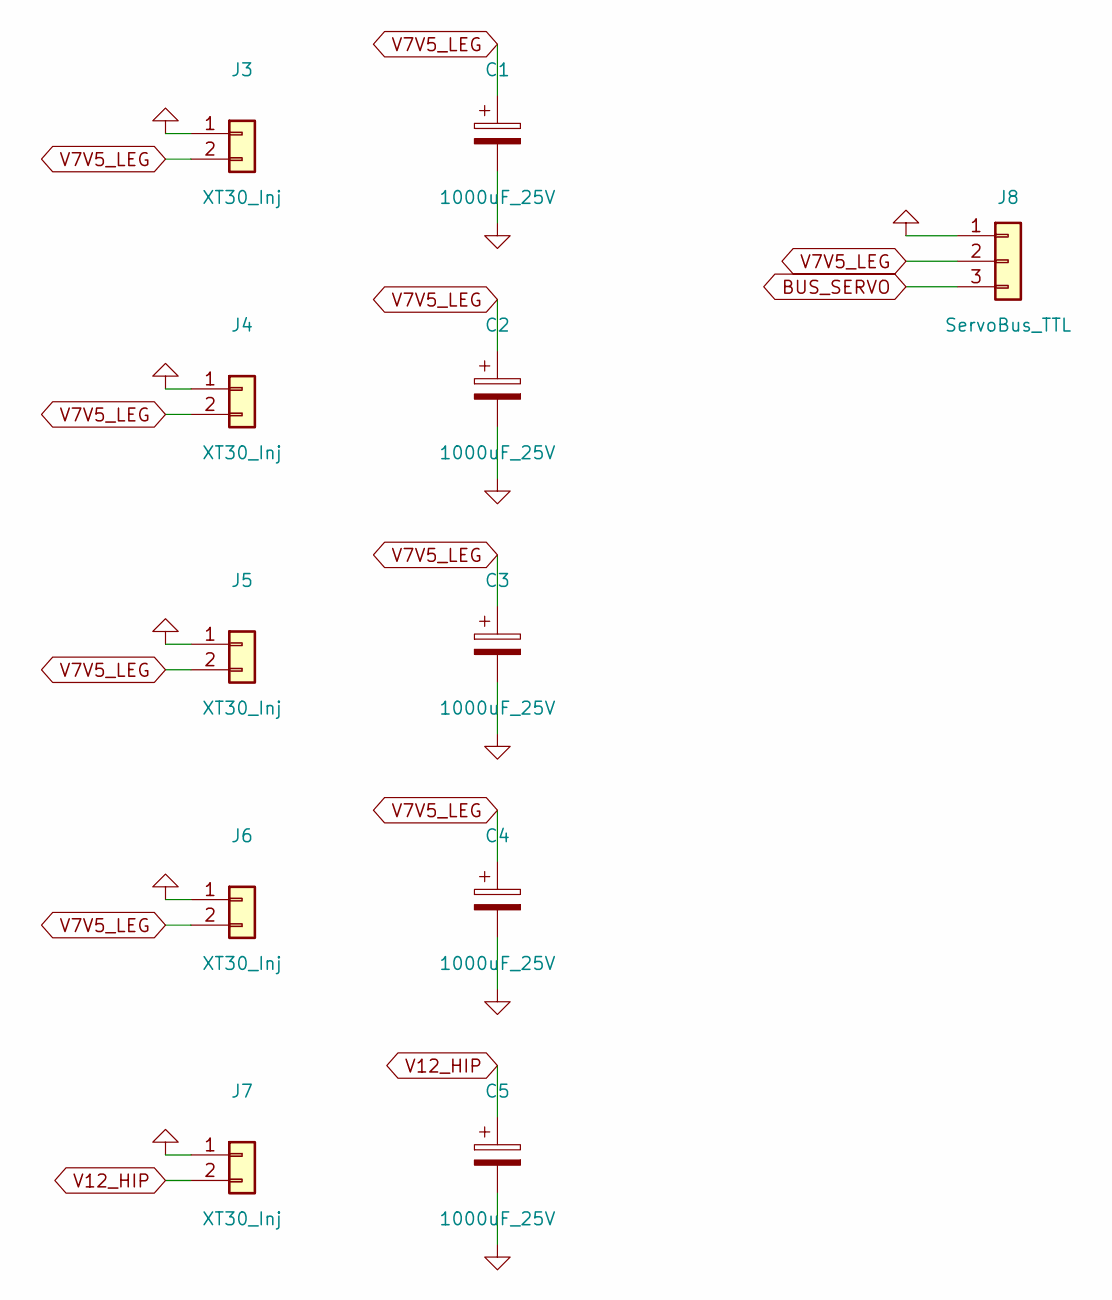
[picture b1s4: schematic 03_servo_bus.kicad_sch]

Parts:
C1, C2, C3, C4, C5: 1000uF_25V; CP_Radial_D12.5mm_P5.00mm; MPN FymuSing-1000uF-25V
J3, J4, J5, J6, J7: XT30_Inj; AMASS_XT30U-M_1x02_P5.0mm_Vertical; MPN XT30U-M
J8: ServoBus_TTL; JST_XH_B3B-XH-A_1x03_P2.50mm_Vertical; MPN B3B-XH-A; DigiKey 455-2248-ND

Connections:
BUS_SERVO: J8.3; also elsewhere on the board
GND: C1.2, C2.2, C3.2, C4.2, C5.2, J3.1, J4.1, J5.1, J6.1, J7.1, J8.1; also elsewhere on the board
V7V5_LEG: C1.1, C2.1, C3.1, C4.1, J3.2, J4.2, J5.2, J6.2, J8.2; also elsewhere on the board
V12_HIP: C5.1, J7.2; also elsewhere on the board

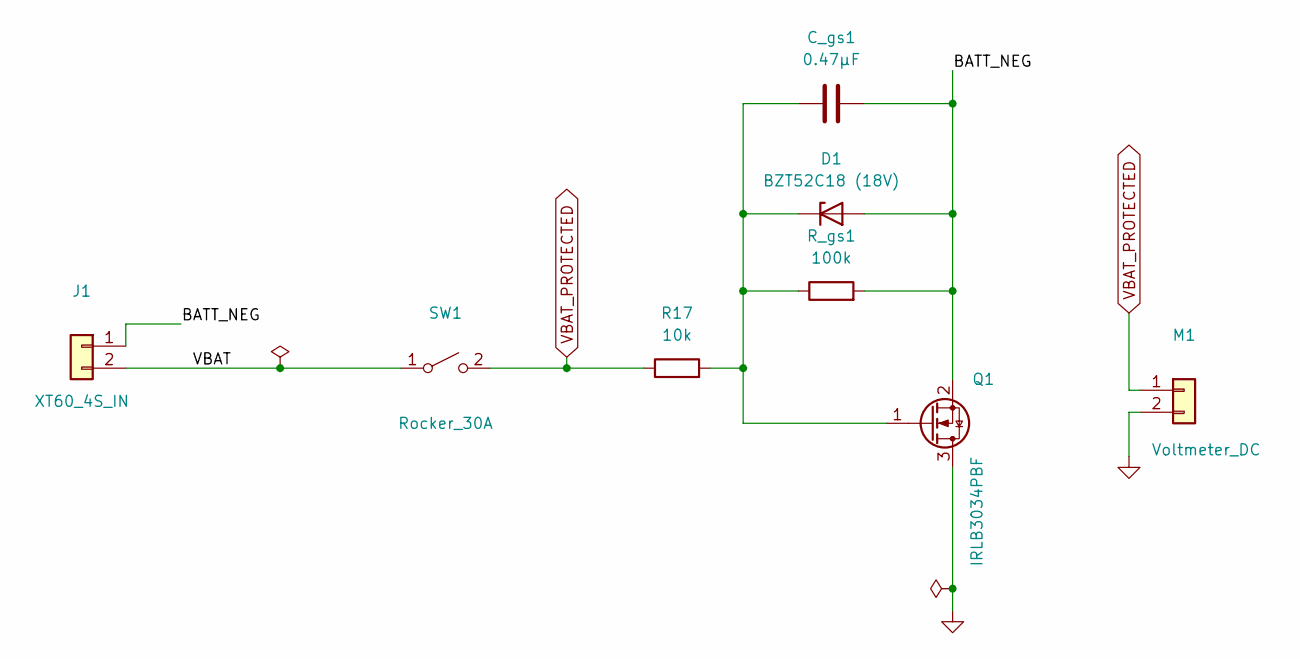
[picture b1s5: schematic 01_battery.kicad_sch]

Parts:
C_gs1: 0.47μF; C_0603_1608Metric
D1: BZT52C18 (18V); D_SOD-123F
J1: XT60_4S_IN; AMASS_XT60-M_1x02_P7.20mm_Vertical; MPN XT60H-M
M1: Voltmeter_DC; PinHeader_1x02_P2.54mm_Vertical; MPN PRPC040SAAN-RC; DigiKey S1011EC-40-ND
Q1: IRLB3034PBF; TO-220-3_Vertical; MPN IRLB3034PBF
R17: 10k; R_0603_1608Metric
R_gs1: 100k; R_0603_1608Metric
SW1: Rocker_30A; TerminalBlock_Philmore_TB132_1x02_P5.00mm_Horizontal; MPN KF301-5.0-2P

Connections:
/01 Battery Input + Reverse Protection/BATT_NEG: C_gs1.2, D1.2 (A), J1.1, Q1.2 (S), R_gs1.2
/01 Battery Input + Reverse Protection/VBAT: J1.2, SW1.1 (A)
GND: M1.2, Q1.3 (D); also elsewhere on the board
unnamed: C_gs1.1, D1.1 (K), Q1.1 (G), R17.2, R_gs1.1
VBAT_PROTECTED: M1.1, R17.1, SW1.2 (B); also elsewhere on the board

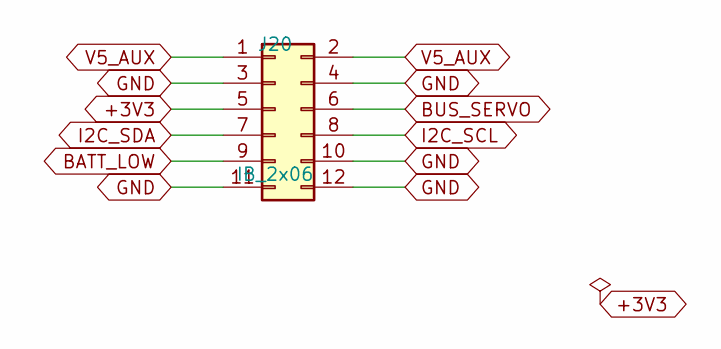
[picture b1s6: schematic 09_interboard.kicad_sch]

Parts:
J20: IB_2x06; IDC-Header_2x06_P2.54mm_Vertical; MPN BHR-12-VUA; DigiKey 2057-BHR-12-VUA-ND

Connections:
+3V3: J20.5; also elsewhere on the board
BATT_LOW: J20.9; also elsewhere on the board
BUS_SERVO: J20.6; also elsewhere on the board
GND: J20.3, J20.4, J20.10, J20.11, J20.12; also elsewhere on the board
I2C_SCL: J20.8; also elsewhere on the board
I2C_SDA: J20.7; also elsewhere on the board
V5_AUX: J20.1, J20.2; also elsewhere on the board

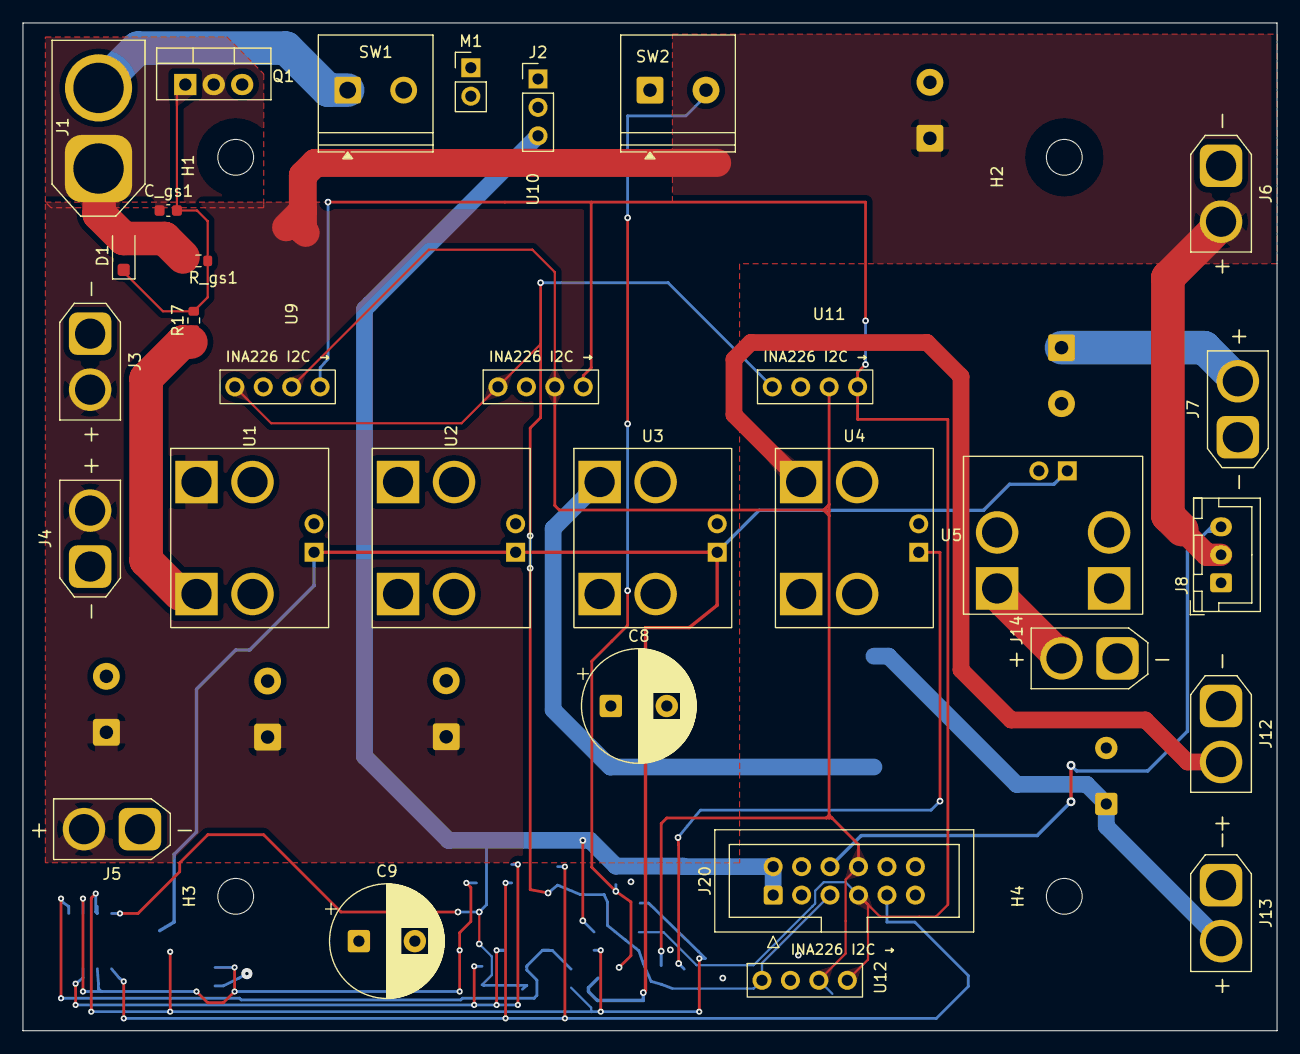
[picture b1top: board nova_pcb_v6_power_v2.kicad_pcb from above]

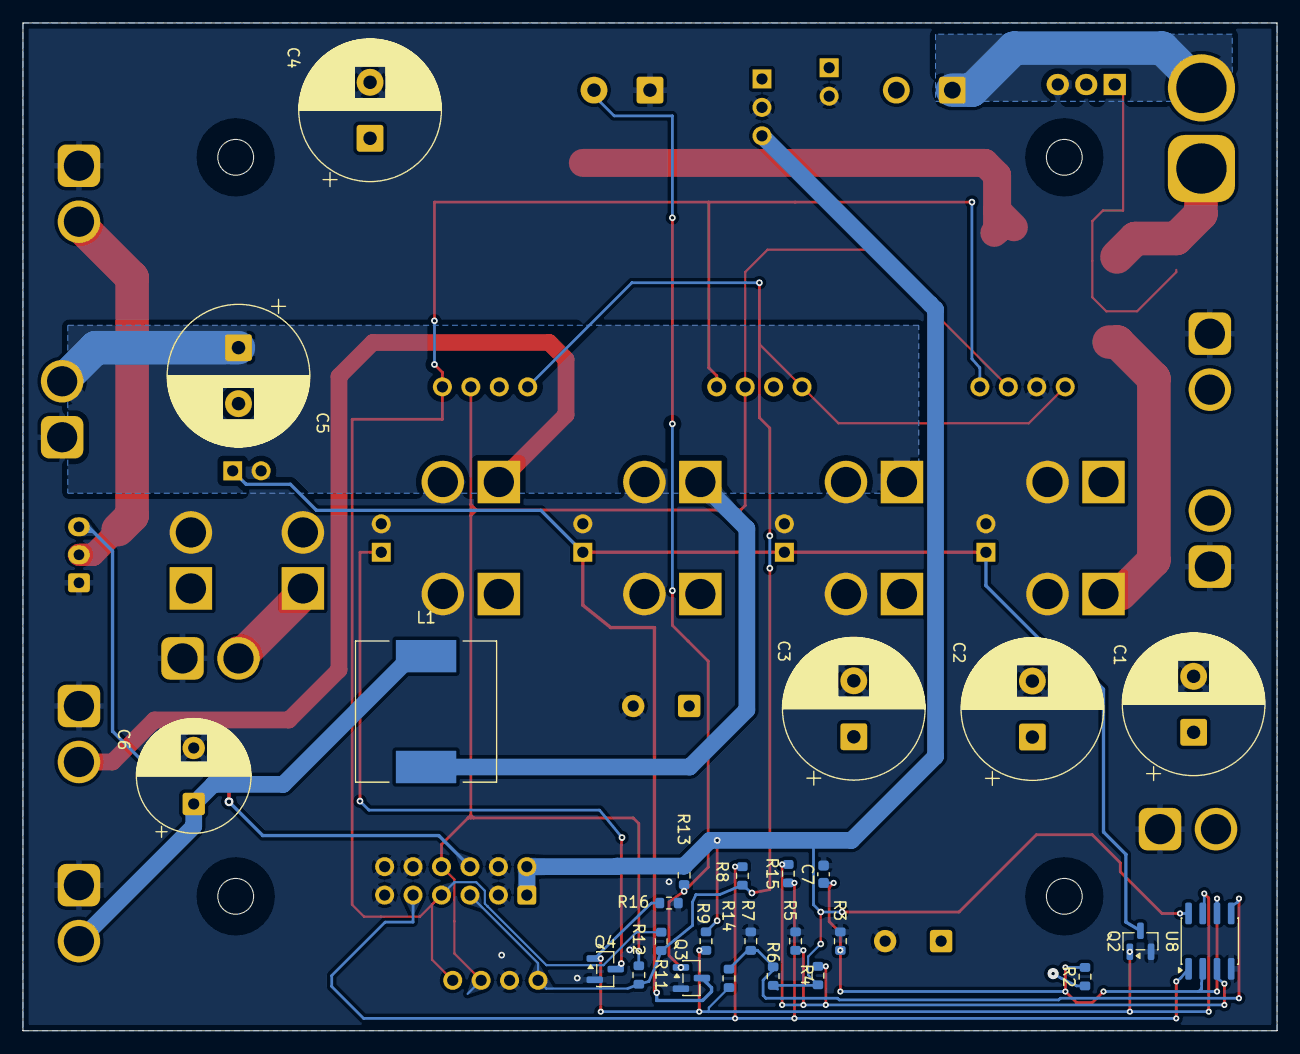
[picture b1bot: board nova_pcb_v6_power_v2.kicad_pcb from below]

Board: 4 copper layers, 112.0 x 90.0 mm, 61 parts (26 on the bottom side), 24 nets.

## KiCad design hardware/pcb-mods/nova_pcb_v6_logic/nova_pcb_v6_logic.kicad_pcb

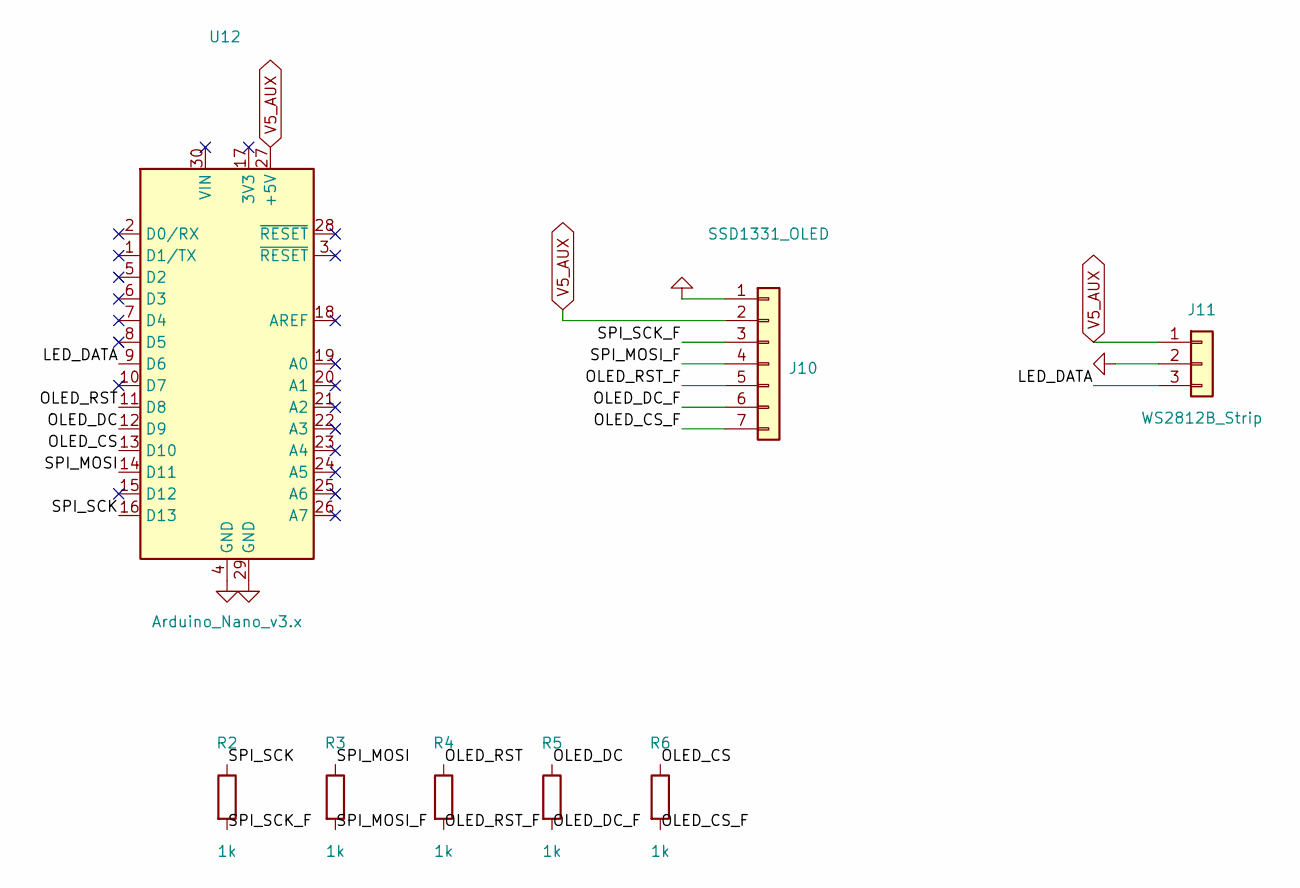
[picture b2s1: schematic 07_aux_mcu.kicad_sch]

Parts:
J10: SSD1331_OLED; PinHeader_1x07_P2.54mm_Vertical
J11: WS2812B_Strip; JST_XH_B3B-XH-A_1x03_P2.50mm_Vertical
R2, R3, R4, R5, R6: 1k; R_0603_1608Metric
U12: Arduino_Nano_v3.x; Arduino_Nano

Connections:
/07 Aux MCU + Peripherals/LED_DATA: J11.3, U12.9 (D6)
/07 Aux MCU + Peripherals/OLED_CS: R6.1, U12.13 (D10)
/07 Aux MCU + Peripherals/OLED_CS_F: J10.7, R6.2
/07 Aux MCU + Peripherals/OLED_DC: R5.1, U12.12 (D9)
/07 Aux MCU + Peripherals/OLED_DC_F: J10.6, R5.2
/07 Aux MCU + Peripherals/OLED_RST: R4.1, U12.11 (D8)
/07 Aux MCU + Peripherals/OLED_RST_F: J10.5, R4.2
/07 Aux MCU + Peripherals/SPI_MOSI: R3.1, U12.14 (D11)
/07 Aux MCU + Peripherals/SPI_MOSI_F: J10.4, R3.2
/07 Aux MCU + Peripherals/SPI_SCK: R2.1, U12.16 (D13)
/07 Aux MCU + Peripherals/SPI_SCK_F: J10.3, R2.2
GND: J10.1, J11.2, U12.4 (GND), U12.29 (GND); also elsewhere on the board
V5_AUX: J10.2, J11.1, U12.27 (+5V); also elsewhere on the board
